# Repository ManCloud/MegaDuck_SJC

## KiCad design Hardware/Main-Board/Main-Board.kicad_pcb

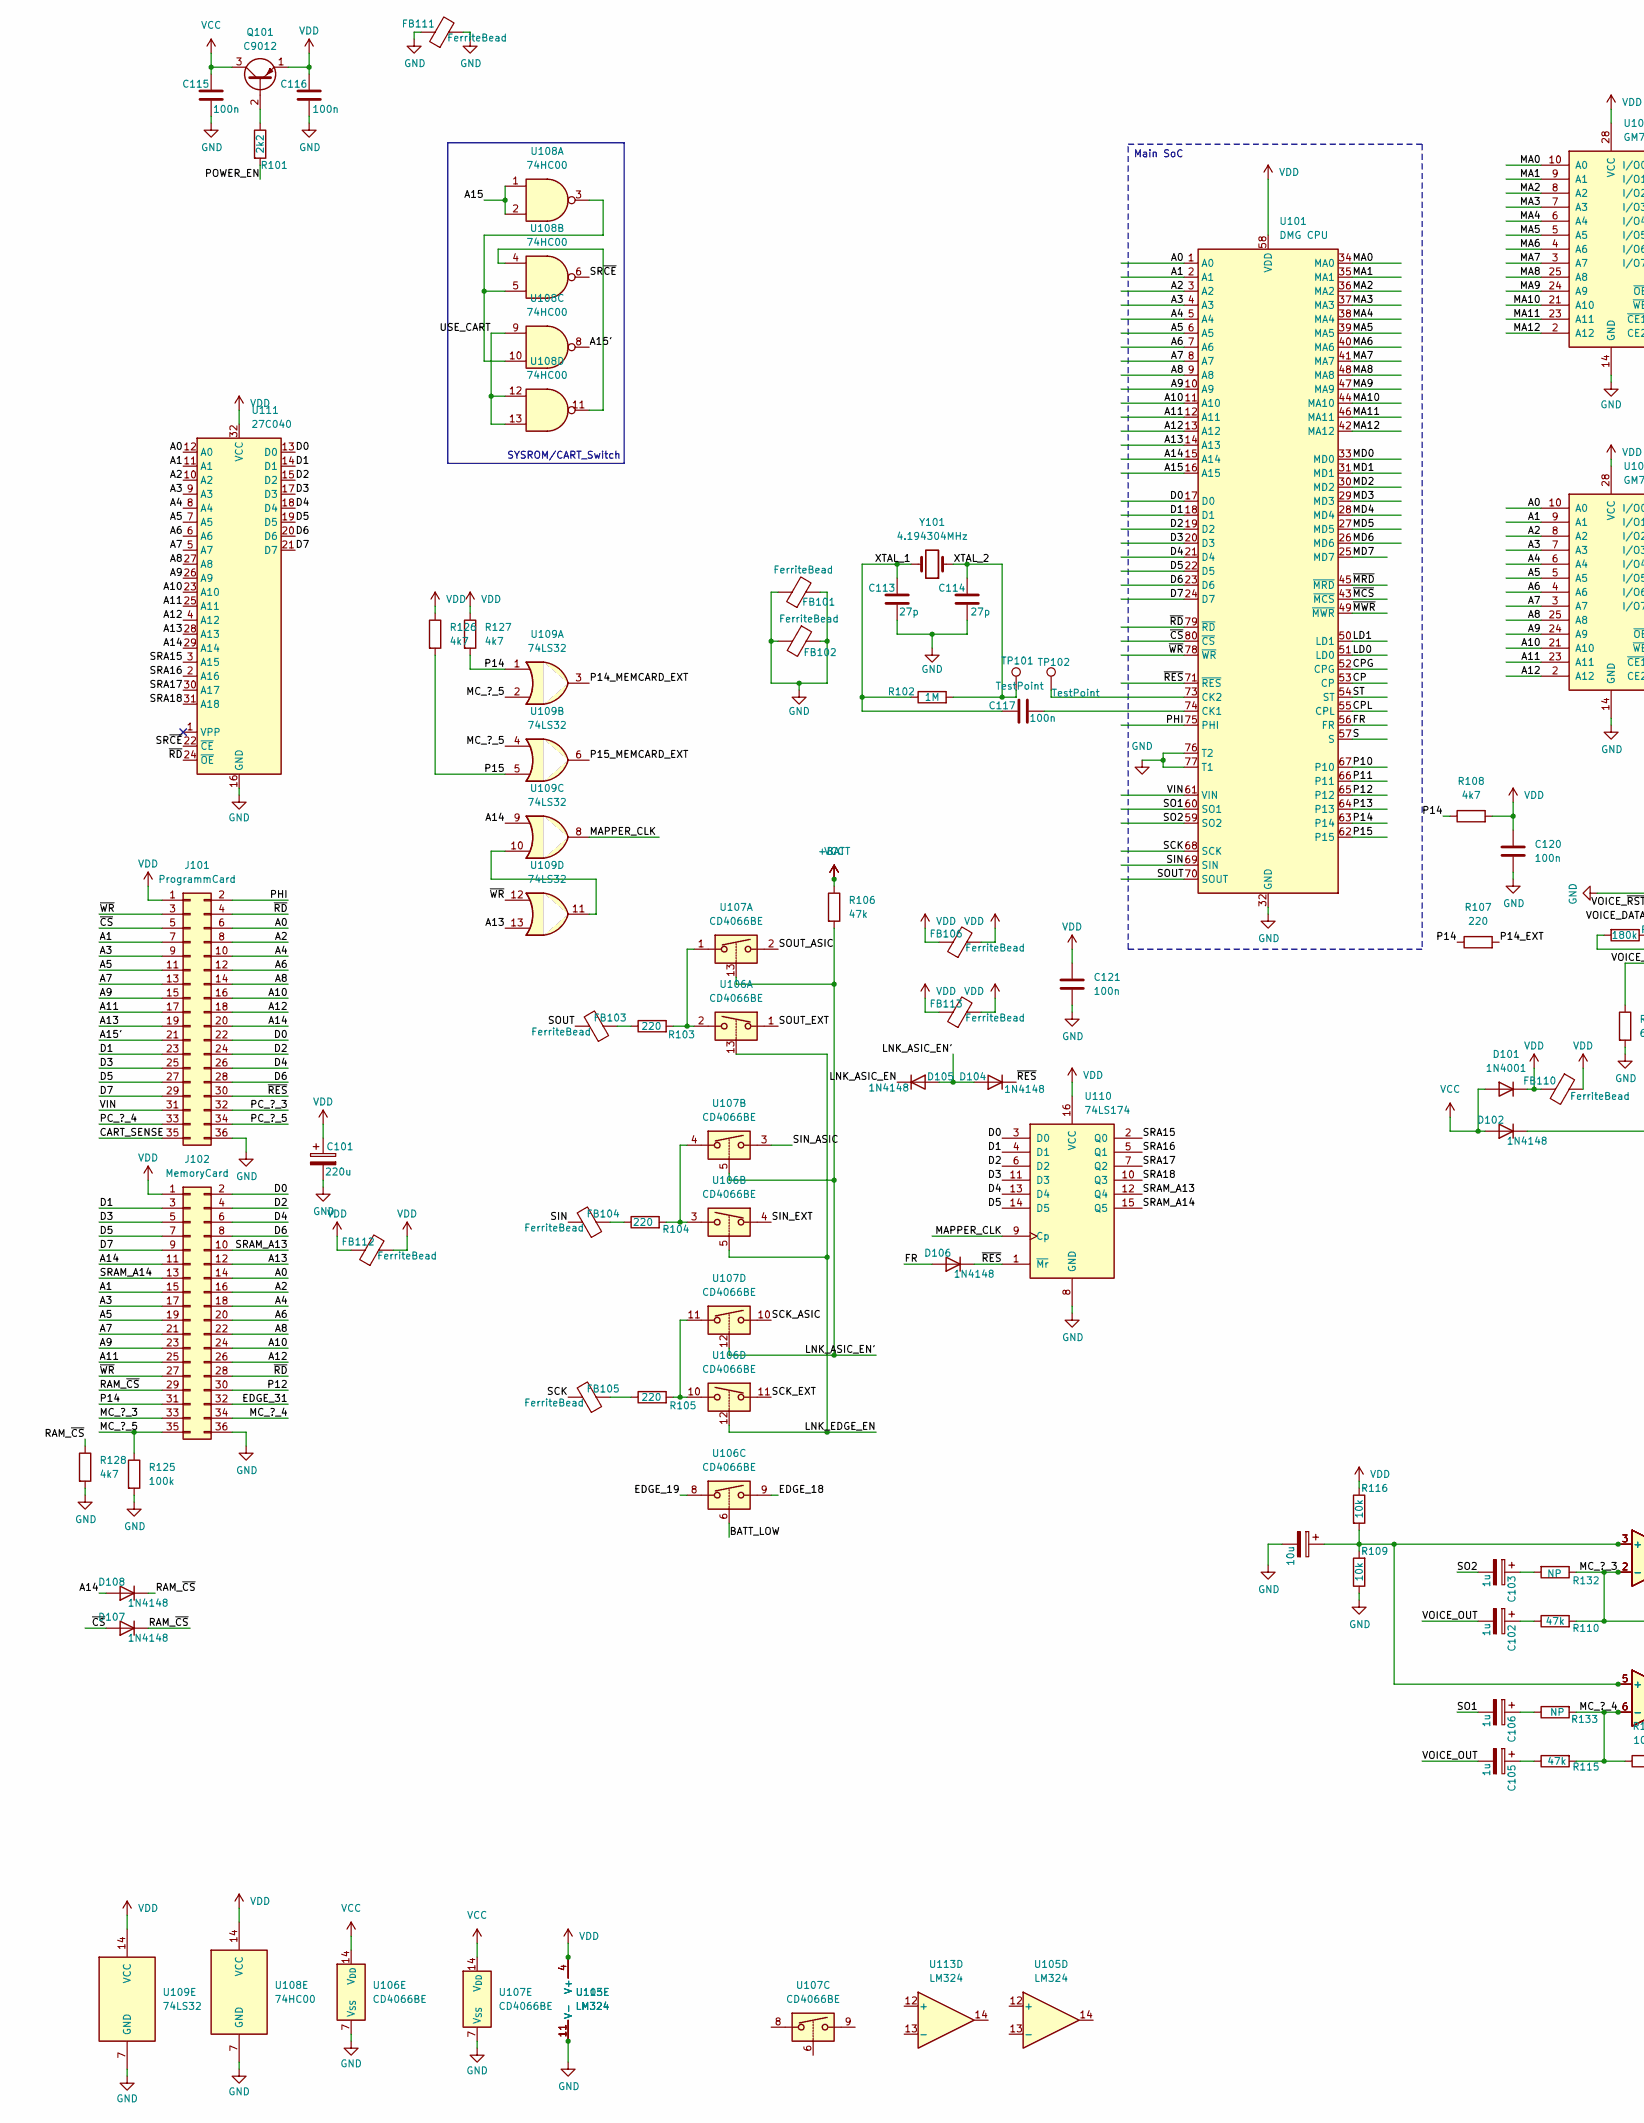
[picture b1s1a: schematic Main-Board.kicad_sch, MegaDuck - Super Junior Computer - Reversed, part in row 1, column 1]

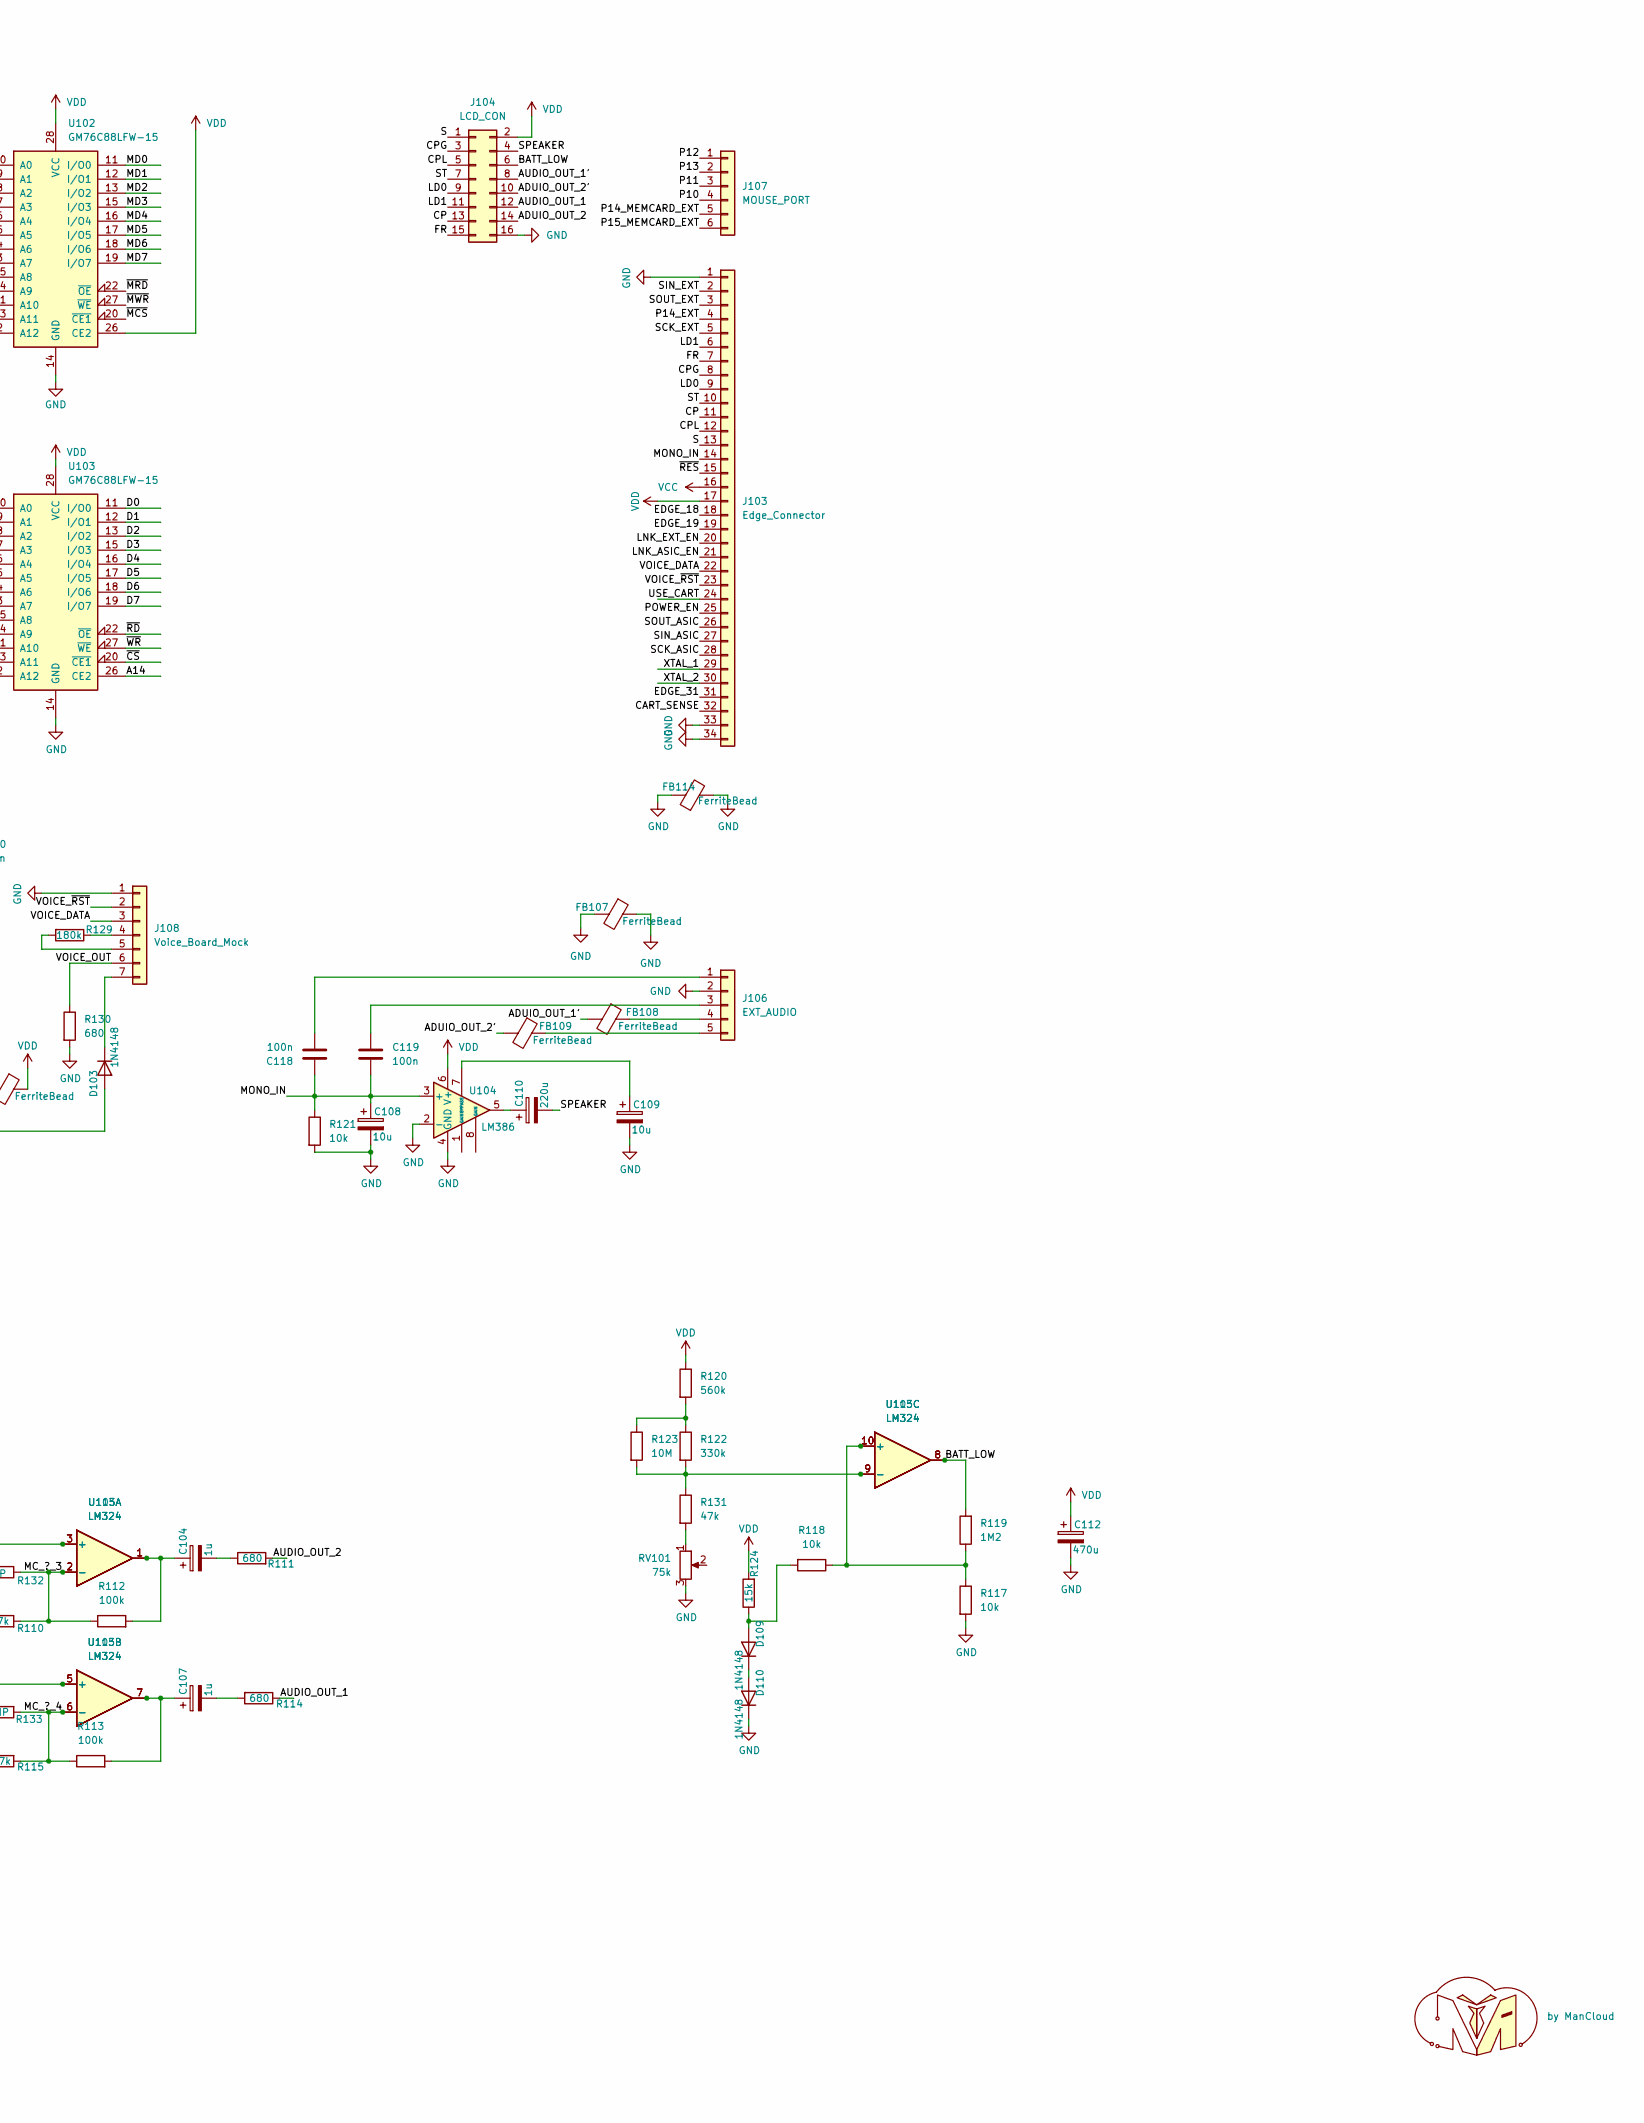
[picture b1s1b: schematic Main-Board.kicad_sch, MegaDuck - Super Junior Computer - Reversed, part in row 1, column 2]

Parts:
C101, C110: 220u; CP_Radial_D6.3mm_P2.50mm
C102, C103, C104, C105, C106, C107: 1u; CP_Radial_D5.0mm_P2.50mm
C108, C109, C111: 10u; CP_Radial_D4.0mm_P2.00mm
C112: 470u; CP_Radial_D6.3mm_P2.50mm
C113, C114: 27p; C_0805_2012Metric
C115, C116, C117, C118, C119, C120, C121: 100n; C_0805_2012Metric
D101: 1N4001; D_A-405_P7.62mm_Horizontal
D102, D103, D104, D105, D106, D107, D108, D109, D110: 1N4148; D_DO-35_SOD27_P7.62mm_Horizontal
FB101, FB102, FB103, FB104, FB105, FB106, FB107, FB108, FB109, FB110, FB111, FB112, FB113, FB114: FerriteBead; L_Axial_L5.3mm_D2.2mm_P2.54mm_Vertical_Vishay_IM-1
J101: ProgrammCard; Edge-Cart-Connector_2x18_P2.54mm_Horizontal
J102: MemoryCard; Edge-Cart-Connector_2x18_P2.54mm_Horizontal
J103: Edge_Connector
J104: LCD_CON; PinHeader_2x08_P2.54mm_Horizontal
J106: EXT_AUDIO; PinHeader_1x05_P2.54mm_Vertical
J107: MOUSE_PORT; Mouse_Connector
J108: Voice_Board_Mock; MD_VoiceChip
Q101: C9012; TO-92_Inline_Wide
R101: 2k2; R_0805_2012Metric
R102: 1M; R_0805_2012Metric
R103, R104, R105, R107: 220; R_0805_2012Metric
R106, R110, R115, R131: 47k; R_0805_2012Metric
R108, R126, R127, R128: 4k7; R_0805_2012Metric
R109, R116, R117, R118, R121: 10k; R_0805_2012Metric
R111, R114, R130: 680; R_0805_2012Metric
R112, R113, R125: 100k; R_0805_2012Metric
R119: 1M2; R_0805_2012Metric
R120: 560k; R_0805_2012Metric
R122: 330k; R_0805_2012Metric
R123: 10M; R_0805_2012Metric
R124: 15k; R_0805_2012Metric
R129: 180k; R_0805_2012Metric
R132, R133: NP; R_0805_2012Metric
RV101: 75k; Potentiometer_Bourns_3296W_Vertical
TP101, TP102: TestPoint; TestPoint_Pad_D1.5mm
U101: DMG CPU; Sharp_QFP-80_14x20mm_P0.8mm
U102, U103: GM76C88LFW-15; Sharp_SOIC-28W_8.6x18mm_P1.27mm
U104: LM386; DIP-8_W7.62mm
U105: LM324; SOIC-14_3.9x8.7mm_P1.27mm
U106, U107: CD4066BE; DIP-14_W7.62mm
U108: 74HC00; DIP-14_W7.62mm
U109: 74LS32; DIP-14_W7.62mm
U110: 74LS174; DIP-16_W7.62mm
U111: 27C040; DIP-32_W15.24mm
U112: by ManCloud
U113: LM324; DIP-14_W7.62mm
Y101: 4.194304MHz; Crystal_HC18-U_Horizontal

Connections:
+BATT: C115.1, D101.2 (A), D102.2 (A), J103.16, Q101.3 (C), R106.1, U106.14 (V_{DD}), U107.14 (V_{DD})
/A0: J101.6, J102.14, U101.1 (A0), U103.10 (A0), U111.12 (A0)
/A1: J101.7, J102.15, U101.2 (A1), U103.9 (A1), U111.11 (A1)
/A2: J101.8, J102.16, U101.3 (A2), U103.8 (A2), U111.10 (A2)
/A3: J101.9, J102.17, U101.4 (A3), U103.7 (A3), U111.9 (A3)
/A4: J101.10, J102.18, U101.5 (A4), U103.6 (A4), U111.8 (A4)
/A5: J101.11, J102.19, U101.6 (A5), U103.5 (A5), U111.7 (A5)
/A6: J101.12, J102.20, U101.7 (A6), U103.4 (A6), U111.6 (A6)
/A7: J101.13, J102.21, U101.8 (A7), U103.3 (A7), U111.5 (A7)
/A8: J101.14, J102.22, U101.9 (A8), U103.25 (A8), U111.27 (A8)
/A9: J101.15, J102.23, U101.10 (A9), U103.24 (A9), U111.26 (A9)
/A10: J101.16, J102.24, U101.11 (A10), U103.21 (A10), U111.23 (A10)
/A11: J101.17, J102.25, U101.12 (A11), U103.23 (A11), U111.25 (A11)
/A12: J101.18, J102.26, U101.13 (A12), U103.2 (A12), U111.4 (A12)
/A13: J101.19, J102.12, U101.14 (A13), U109.13, U111.28 (A13)
/A14: D108.2 (A), J101.20, J102.11, U101.15 (A14), U103.26 (CE2), U109.9, U111.29 (A14)
/A15: U101.16 (A15), U108.1, U108.2
/A15': J101.21, U108.8
/ADUIO_OUT_1': FB108.2
/ADUIO_OUT_2: J104.14
/ADUIO_OUT_2': FB109.2, J104.10
/AUDIO_OUT_1: J104.12, R114.1
/AUDIO_OUT_1': J104.8
/AUDIO_OUT_2: R111.2
/BATT_LOW: J104.6, R119.2, U105.8, U106.6, U113.8
/CART_SENSE: J101.35, J103.32
/CP: J103.11, J104.13, U101.53 (CP)
/CPG: J103.8, J104.3, U101.52 (CPG)
/CPL: J103.12, J104.5, U101.55 (CPL)
/D0: J101.22, J102.2, U101.17 (D0), U103.11 (I/O0), U110.3 (D0), U111.13 (D0)
/D1: J101.23, J102.3, U101.18 (D1), U103.12 (I/O1), U110.4 (D1), U111.14 (D1)
/D2: J101.24, J102.4, U101.19 (D2), U103.13 (I/O2), U110.6 (D2), U111.15 (D2)
/D3: J101.25, J102.5, U101.20 (D3), U103.15 (I/O3), U110.11 (D3), U111.17 (D3)
/D4: J101.26, J102.6, U101.21 (D4), U103.16 (I/O4), U110.13 (D4), U111.18 (D4)
/D5: J101.27, J102.7, U101.22 (D5), U103.17 (I/O5), U110.14 (D5), U111.19 (D5)
/D6: J101.28, J102.8, U101.23 (D6), U103.18 (I/O6), U111.20 (D6)
/D7: J101.29, J102.9, U101.24 (D7), U103.19 (I/O7), U111.21 (D7)
/EDGE_18: J103.18, U106.9
/EDGE_19: J103.19, U106.8
/EDGE_31: J102.32, J103.31
/FR: D106.2 (A), J103.7, J104.15, U101.56 (FR)
/LD0: J103.9, J104.9, U101.51 (LD0)
/LD1: J103.6, J104.11, U101.50 (LD1)
/LNK_ASIC_EN: D105.1 (K), J103.21
/LNK_ASIC_EN': D104.2 (A), D105.2 (A), R106.2, U107.5, U107.12, U107.13
/LNK_EDGE_EN: U106.5, U106.12, U106.13
/LNK_EXT_EN: J103.20
/MA0: U101.34 (MA0), U102.10 (A0)
/MA1: U101.35 (MA1), U102.9 (A1)
/MA2: U101.36 (MA2), U102.8 (A2)
/MA3: U101.37 (MA3), U102.7 (A3)
/MA4: U101.38 (MA4), U102.6 (A4)
/MA5: U101.39 (MA5), U102.5 (A5)
/MA6: U101.40 (MA6), U102.4 (A6)
/MA7: U101.41 (MA7), U102.3 (A7)
/MA8: U101.48 (MA8), U102.25 (A8)
/MA9: U101.47 (MA9), U102.24 (A9)
/MA10: U101.44 (MA10), U102.21 (A10)
/MA11: U101.46 (MA11), U102.23 (A11)
/MA12: U101.42 (MA12), U102.2 (A12)
/MAPPER_CLK: U109.8, U110.9 (Cp)
/MC_?_3: J102.33, R110.2, R112.1, R132.1, U105.2 (-), U113.2 (-)
/MC_?_4: J102.34, R113.1, R115.2, R133.2, U105.6 (-), U113.6 (-)
/MC_?_5: J102.35, R125.1, U109.2, U109.4
/MD0: U101.33 (MD0), U102.11 (I/O0)
/MD1: U101.31 (MD1), U102.12 (I/O1)
/MD2: U101.30 (MD2), U102.13 (I/O2)
/MD3: U101.29 (MD3), U102.15 (I/O3)
/MD4: U101.28 (MD4), U102.16 (I/O4)
/MD5: U101.27 (MD5), U102.17 (I/O5)
/MD6: U101.26 (MD6), U102.18 (I/O6)
/MD7: U101.25 (MD7), U102.19 (I/O7)
/MONO_IN: C108.1, C118.1, C119.2, J103.14, R121.1, U104.3 (+)
/P10: J107.4, U101.67 (P10)
/P11: J107.3, U101.66 (P11)
/P12: J102.30, J107.1, U101.65 (P12)
/P13: J107.2, U101.64 (P13)
/P14: J102.31, R107.1, R108.1, R127.2, U101.63 (P14), U109.1
/P14_EXT: J103.4, R107.2
/P14_MEMCARD_EXT: J107.5, U109.3
/P15: R126.2, U101.62 (P15), U109.5
/P15_MEMCARD_EXT: J107.6, U109.6
/PC_?_3: J101.32
/PC_?_4: J101.33
/PC_?_5: J101.34
/PHI: J101.2, U101.75 (PHI)
/POWER_EN: J103.25, R101.2
/RAM_~CS: D107.1 (K), D108.1 (K), J102.29, R128.1
/S: J103.13, J104.1, U101.57 (S)
/SCK: FB105.2, U101.68 (SCK)
/SCK_ASIC: J103.28, U107.10
/SCK_EXT: J103.5, U106.11
/SIN: FB104.2, U101.69 (SIN)
/SIN_ASIC: J103.27, U107.3
/SIN_EXT: J103.2, U106.4
/SO1: C106.2, U101.60 (SO1)
/SO2: C103.2, U101.59 (SO2)
/SOUT: FB103.2, U101.70 (SOUT)
/SOUT_ASIC: J103.26, U107.2
/SOUT_EXT: J103.3, U106.1
/SPEAKER: C110.2, J104.4
/SRA15: U110.2 (Q0), U111.3 (A15)
/SRA16: U110.5 (Q1), U111.2 (A16)
/SRA17: U110.7 (Q2), U111.30 (A17)
/SRA18: U110.10 (Q3), U111.31 (A18)
/SRAM_A13: J102.10, U110.12 (Q4)
/SRAM_A14: J102.13, U110.15 (Q5)
/SR~CE: U108.6, U111.22 (~CE)
/ST: J103.10, J104.7, U101.54 (ST)
/USE_CART: J103.24, U108.9, U108.12, U108.13
/VIN: J101.31, U101.61 (VIN)
/VOICE_DATA: J103.22, J108.3
/VOICE_OUT: C102.2, C105.2, J108.6, R130.1
/VOICE_~RST: J103.23, J108.2
/XTAL_1: C113.1, C117.2, J103.29, R102.1, Y101.2
/XTAL_2: C114.1, J103.30, R102.2, TP101.1, Y101.1
/~CS: D107.2 (A), J101.5, U101.80 (~CS), U103.20 (~CE1)
/~MCS: U101.43 (~MCS), U102.20 (~CE1)
/~MRD: U101.45 (~MRD), U102.22 (~OE)
/~MWR: U101.49 (~MWR), U102.27 (~WE)
/~RD: J101.4, J102.28, U101.79 (~RD), U103.22 (~OE), U111.24 (~OE)
/~RES: D104.1 (K), D106.1 (K), J101.30, J103.15, U101.71 (~RES), U110.1 (~Mr)
/~WR: J101.3, J102.27, U101.78 (~WR), U103.27 (~WE), U109.12
GND: C101.2, C108.2, C109.2, C111.2, C112.2, C113.2, C114.2, C115.2, C116.2, C120.1, C121.2, D110.1 (K), FB101.1, FB101.2, FB102.1, FB102.2, FB107.1, FB107.2, FB111.1, FB111.2, FB114.1, FB114.2, J101.36, J102.36, J103.1, J103.33, J103.34, J104.16, J106.2, J108.1, R109.1, R117.2, R121.2, R125.2, R128.2, R130.2, RV101.3, U101.32 (GND), U101.72 (GND), U101.76 (T2), U101.77 (T1), U102.14 (GND), U103.14 (GND), U104.2 (-), U104.4 (GND), U105.11 (V-), U106.7 (V_{SS}), U107.7 (V_{SS}), U108.7 (GND), U109.7 (GND), U110.8 (GND), U111.16 (GND), U113.11 (V-)
unnamed: C102.1, R110.1
unnamed: C103.1, R132.2
unnamed: C104.1, R112.2, U105.1, U113.1
unnamed: C104.2, R111.1
unnamed: C105.1, R115.1
unnamed: C106.1, R133.1
unnamed: C107.1, R113.2, U105.7, U113.7
unnamed: C107.2, R114.2
unnamed: C110.1, U104.5
unnamed: D102.1 (K), D103.2 (A)
unnamed: D103.1 (K), J108.7
unnamed: D109.2 (A), R118.2, R124.1
unnamed: D109.1 (K), D110.2 (A)
unnamed: FB103.1, R103.1
unnamed: FB104.1, R104.1
unnamed: FB105.1, R105.1
unnamed: C118.2, J106.1
unnamed: C119.1, J106.3
unnamed: FB108.1, J106.4
unnamed: FB109.1, J106.5
unnamed: J108.4, R129.1
unnamed: J108.5, R129.2
unnamed: Q101.2 (B), R101.1
unnamed: R103.2, U106.2, U107.1
unnamed: R104.2, U106.3, U107.4
unnamed: R105.2, U106.10, U107.11
unnamed: R120.2, R122.1, R123.1
unnamed: R131.2, RV101.1
unnamed: C117.1, U101.74 (CK1)
unnamed: TP102.1, U101.73 (CK2)
unnamed: C109.1, U104.7 (BYPASS)
unnamed: C111.1, R109.2, R116.2, U105.3 (+), U105.5 (+), U113.3 (+), U113.5 (+)
unnamed: R117.1, R118.1, R119.1, U105.10 (+), U113.10 (+)
unnamed: R122.2, R123.2, R131.1, U105.9 (-), U113.9 (-)
unnamed: U108.3, U108.5, U108.10
unnamed: U108.4, U108.11
unnamed: U109.10, U109.11
VDD: C101.1, C112.1, C116.1, C120.2, C121.1, D101.1 (K), FB106.1, FB106.2, FB110.1, FB110.2, FB112.1, FB112.2, FB113.1, FB113.2, J101.1, J102.1, J103.17, J104.2, Q101.1 (E), R108.2, R116.1, R120.1, R124.2, R126.1, R127.1, U101.58 (VDD), U102.26 (CE2), U102.28 (VCC), U103.28 (VCC), U104.6 (V+), U105.4 (V+), U108.14 (VCC), U109.14 (VCC), U110.16 (VCC), U111.32 (VCC), U113.4 (V+)

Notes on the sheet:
SYSROM/CART_Switch
Main SoC

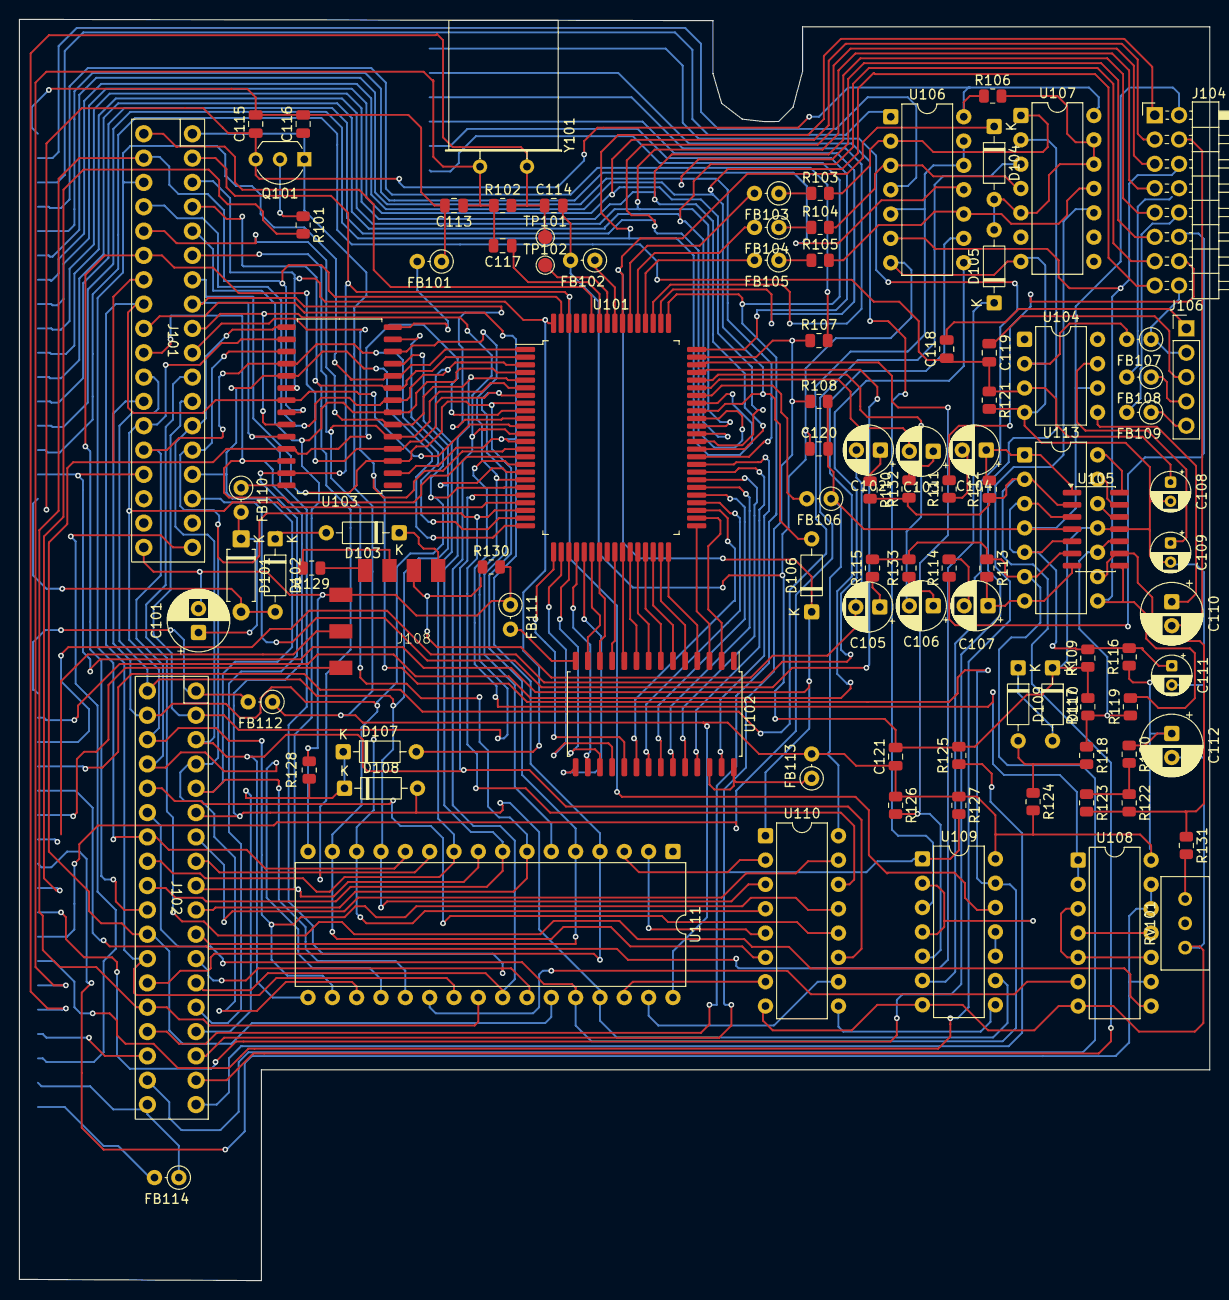
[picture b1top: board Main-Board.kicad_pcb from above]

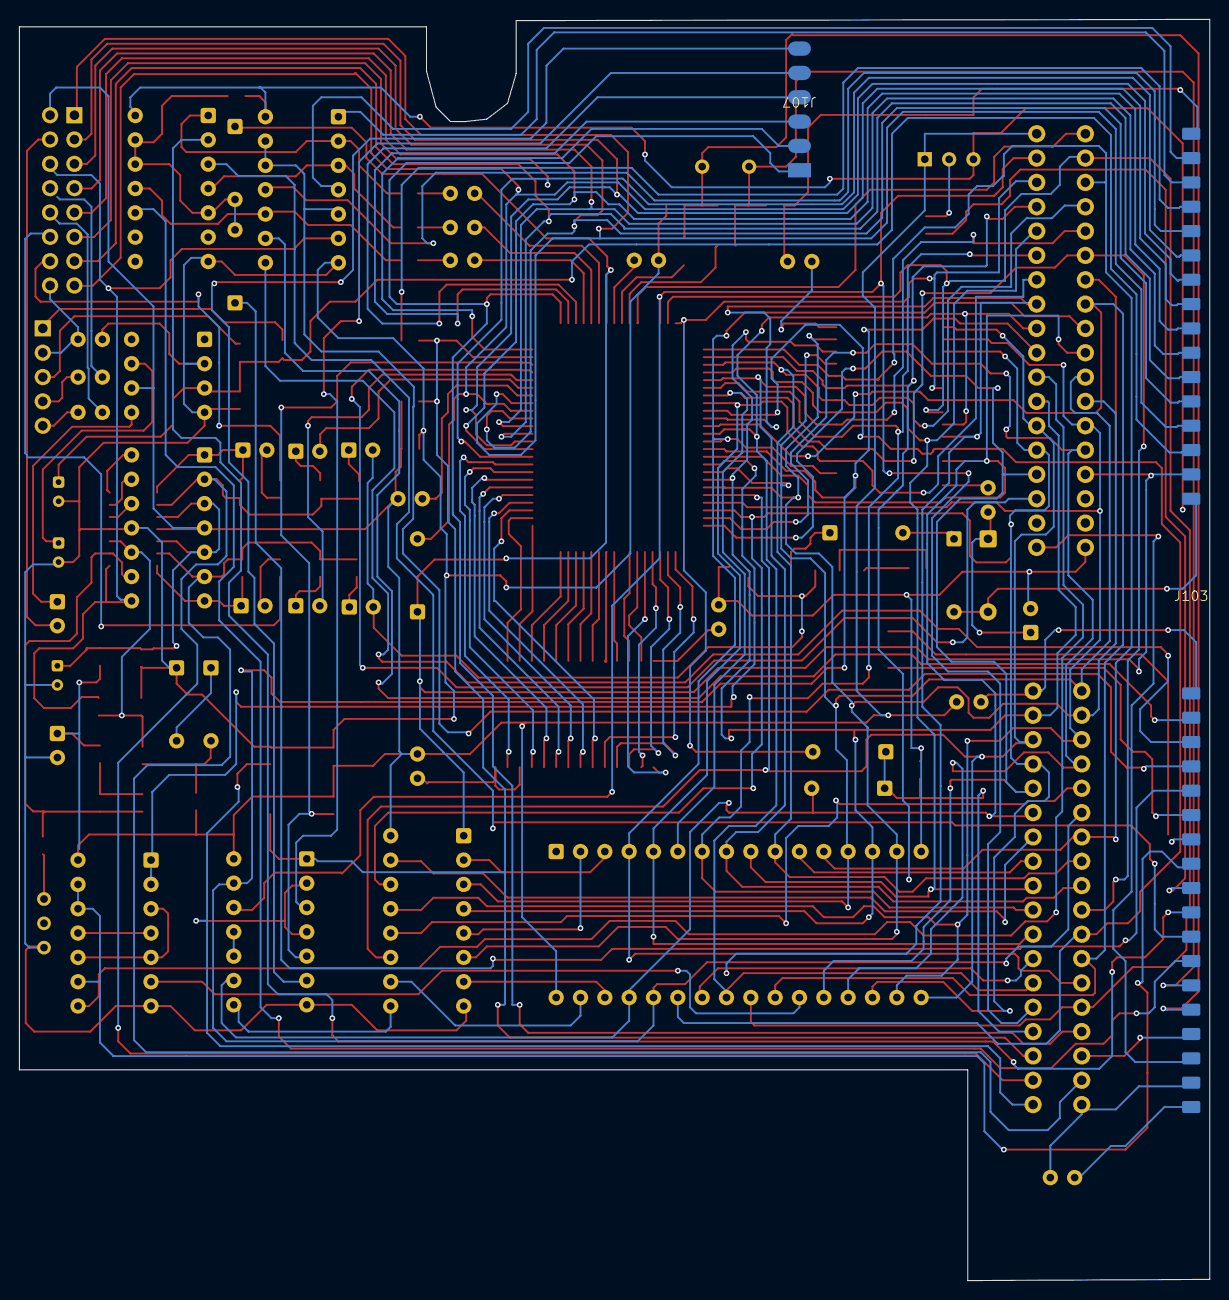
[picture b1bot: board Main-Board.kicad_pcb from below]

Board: 2 copper layers, 124.3 x 131.7 mm, 102 parts (2 on the bottom side), 154 nets.

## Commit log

2025-12-12 Initial Commit.
    Traced:
    EXT-Board
    ASIC-Board
    Parts Only:
    Main-Board
    Changes to be committed:
2025-12-16 Finished work on Mainboard
    * Complete reversed Schematic incl. Signal "assumptions"
    * Complete traced MainBoard-PCB
2025-12-17 Split Schematics to different projects
2025-12-17 added schematics-pdf and board pictures
2025-12-18 fixed orientation of EXT-Header
2025-12-18 Fixed error in Audio-Mixer - Added more signal names
